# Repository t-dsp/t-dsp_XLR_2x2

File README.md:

# T-DSP XLR 2×2 — Balanced XLR I/O Board

**Part of the [T-DSP](https://t-dsp.com) open modular audio platform.**

A simple balanced-audio I/O board: **two XLR inputs and two XLR outputs** for pro line-level signals. It hosts a [T-DSP TAC5212 pro audio module](https://github.com/t-dsp/t-dsp_tac5212_pro_audio_module), which handles the entire analog signal path. Audio and control (I2S + I2C) are carried over a ribbon cable to a separate [T-DSP](https://t-dsp.com) controller module — this board has no microcontroller of its own.

| | |
|:---:|:---:|
|  |  |
|  |  |

**[View 3D Render Gallery](https://t-dsp.github.io/t-dsp_XLR_2x2/gallery.html)** -- interactive slideshow of all board views

## What It Is

This is a **balanced I/O carrier** for the T-DSP ecosystem. It exposes four panel-mount Neutrik XLR connectors and gives a [TAC5212 pro audio module](https://github.com/t-dsp/t-dsp_tac5212_pro_audio_module) a home:

- **2× XLR inputs** — balanced, pro line level, into the TAC5212 ADC
- **2× XLR outputs** — balanced, pro line level, from the TAC5212 DAC
- **TAC5212 module socket** — the codec daughter board mounts here and does all the analog work
- **Ribbon link** — I2S audio, I2C control, and power travel over a single 2×10 ribbon cable to the host controller

There is no microcontroller, DSP, or power supply on this board. It is purely the analog front panel: connectors, the codec module, and the cable to the brains.

## How It Fits Together

```
  XLR in  ─┐                                  ┌─ I2S (audio)
  XLR in  ─┼─►  TAC5212 module  ◄────ribbon───┼─ I2C (control)   ►  T-DSP controller
  XLR out ─┤      (this board)                └─ power              (Teensy-based)
  XLR out ─┘
```

The controller module runs the firmware and clocks; this board provides the balanced analog I/O and the codec that converts it.

## Features

### Audio I/O
- **2× balanced XLR input** — female XLR (Neutrik NC3FAH2), into the TAC5212 ADC
- **2× balanced XLR output** — male XLR (Neutrik NC3MAH), from the TAC5212 DAC
- Pro line-level signal path, handled entirely by the TAC5212 module

### Connectivity
- **TAC5212 module socket** — hosts the [T-DSP TAC5212 pro audio module](https://github.com/t-dsp/t-dsp_tac5212_pro_audio_module)
- **2×10 ribbon header** — carries I2S, I2C, and power to/from a T-DSP controller module

### Power
- Supplied from the host controller over the ribbon cable — no power input on this board

## Board Design

- **100 mm × 44 mm** PCB
- Built around the T-DSP audio module board-outline standard (50 × 34.5 mm module footprint)
- The TAC5212 module handles the entire analog signal path
- KiCad source files, full BOM, and CI-generated manufacturing outputs included
- Open source under CC BY-NC-SA 4.0

## Getting Started

### Hardware

1. Mount the **TAC5212 pro audio module** onto this board's module socket
2. Wire the four panel-mount **XLR connectors** (2 in, 2 out)
3. Connect the **2×10 ribbon cable** between this board and your T-DSP controller module
4. Power and clocks are provided by the controller over the ribbon — no separate supply needed

### Firmware

The TAC5212 codec is configured and clocked by the **host controller module**, not by this board. See [t-dsp_software](https://github.com/t-dsp/t-dsp_software) for the firmware that drives the codec over I2C and streams audio over I2S.

View the design files in your browser with KiCanvas: [Schematic](https://kicanvas.org/?github=https://github.com/t-dsp/t-dsp_XLR_2x2/blob/main/t-dsp_XLR_2x2.kicad_sch) | [PCB](https://kicanvas.org/?github=https://github.com/t-dsp/t-dsp_XLR_2x2/blob/main/t-dsp_XLR_2x2.kicad_pcb)

## Project Files

| Directory | Contents |
|-----------|----------|
| `/3d_models/` | 3D models for PCB components |
| `/lib_fp/` | Custom KiCad footprint libraries |
| `/lib_sch/` | Custom KiCad schematic symbol libraries |
| `/manufacturing/` | CI-generated manufacturing outputs (gerbers, BOM, pick & place, PDFs) |
| `/pages/` | [3D Render Gallery](https://t-dsp.github.io/t-dsp_XLR_2x2/gallery.html), [Interactive BOM](https://t-dsp.github.io/t-dsp_XLR_2x2/ibom.html) |

## Manufacturing

Manufacturing files are generated automatically by [KiBot](https://github.com/INTI-CMNB/KiBot) on every push to `main` and on tagged releases via GitHub Actions.

To order:
1. Download the latest `t-dsp_XLR_2x2-manufacturing-vX.X.zip` from [Releases](https://github.com/t-dsp/t-dsp_XLR_2x2/releases)
2. Upload gerbers and drill files to your PCB fab (JLCPCB, PCBWay, etc.)
3. Use the BOM and CPL files for JLCPCB SMT assembly

## About T-DSP

T-DSP is an open modular audio platform built around the Teensy microcontroller and the [Teensy Audio Library](https://www.pjrc.com/teensy/td_libs_Audio.html). This board is the balanced-I/O front end — a clean 2-in/2-out XLR interface that pairs a TAC5212 codec module with a T-DSP controller over a ribbon cable.

For a full audio development platform — a 4-layer backplane pairing a Teensy 4.1, an ESP32, and the TAC5212 codec module — see the [T-DSP Core](https://github.com/t-dsp/t-dsp_core).

Learn more at [t-dsp.com](https://t-dsp.com).

## Status

Active development. If you build one, please open an issue or reach out.

## Contact

For consulting, custom audio hardware design, or commercial licensing, reach out via [LinkedIn](https://linkedin.com/in/jayshoe).

## License

[Creative Commons Attribution-NonCommercial-ShareAlike 4.0 International (CC BY-NC-SA 4.0)](https://creativecommons.org/licenses/by-nc-sa/4.0/)

Free to share and adapt for non-commercial purposes with attribution and same license on derivatives.

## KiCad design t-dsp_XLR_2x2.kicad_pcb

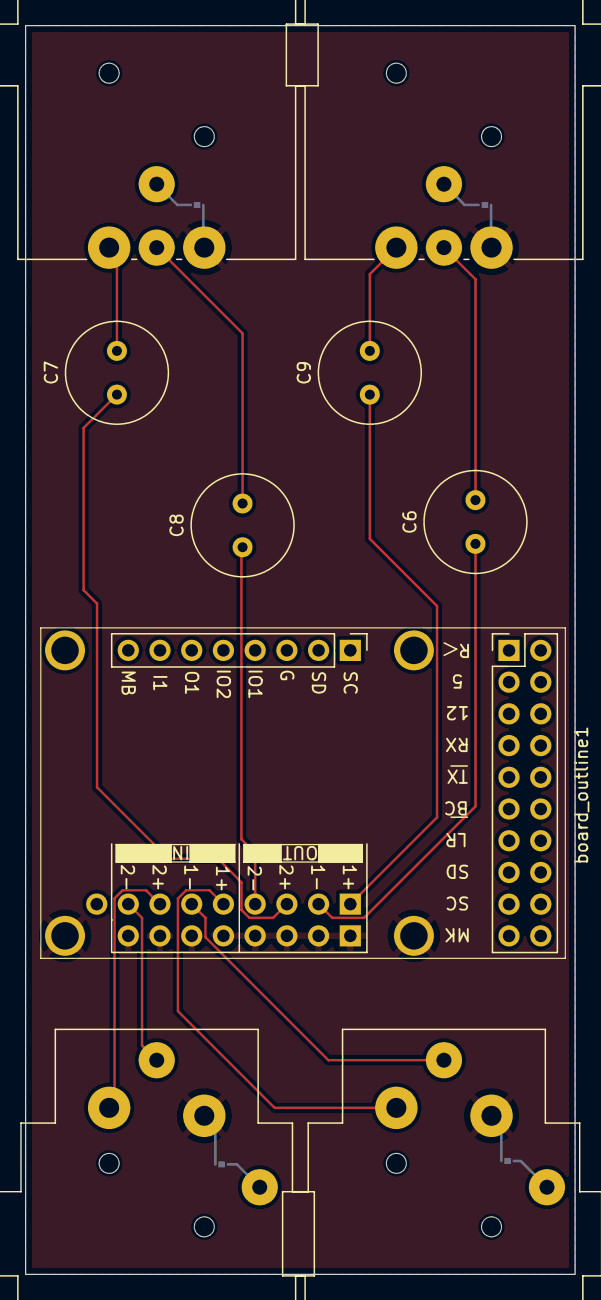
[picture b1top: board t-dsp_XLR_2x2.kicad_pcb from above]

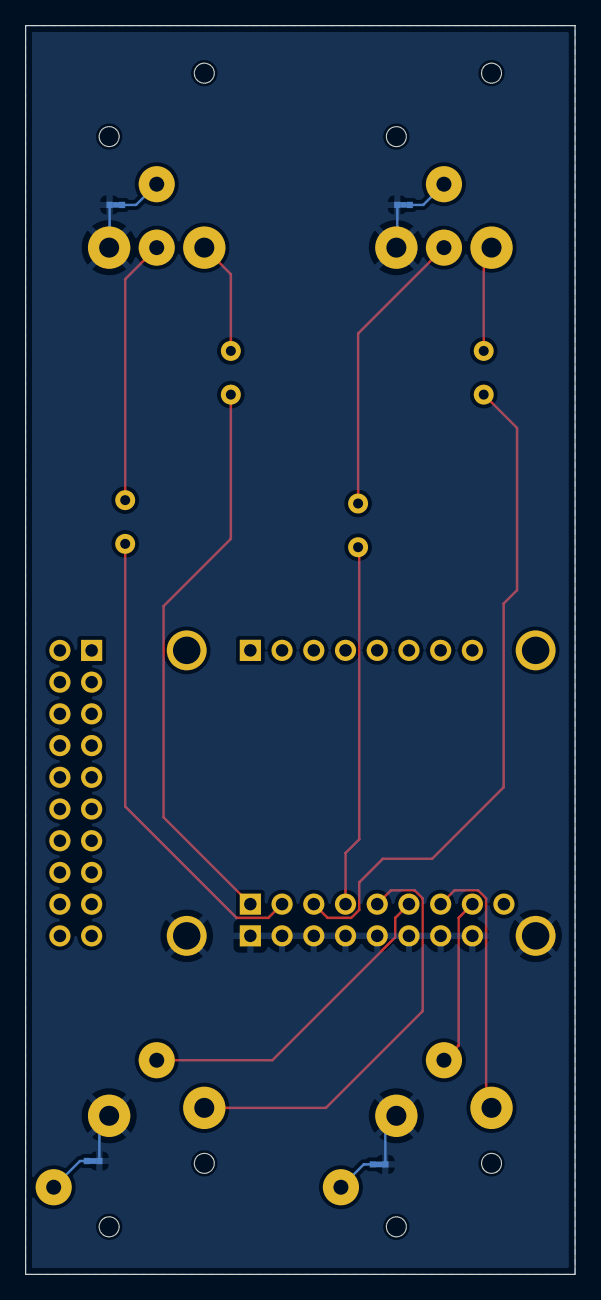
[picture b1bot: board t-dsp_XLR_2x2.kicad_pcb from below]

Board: 2 copper layers, 44.0 x 100.0 mm, 14 parts (4 on the bottom side), 17 nets.

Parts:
B1: Board; audio_project_board_outline_100x50_nm
C6, C7, C8, C9: 470 uF Electrolytic Audio-Grade; C_Radial_D8.0mm_H11.5mm_P3.50mm
G4, G5, G7, G8: jumper; jumper_slice
J30, J31: NC3FAH; Jack_XLR_Neutrik_NC3FAH2_Horizontal
XLRM1, XLRM2: XLRM_NC3MAH
board_outline1: TAC5212 Module; audio_module_board_outline_50x34.5_d1

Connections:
/AUDIO_IN1M: J30.3, board_outline1.31 (IN1M)
/AUDIO_IN1P: J30.2, board_outline1.29 (IN1P)
/AUDIO_IN2M: J31.3, board_outline1.35 (IN2M)
/AUDIO_IN2P: J31.2, board_outline1.33 (IN2P)
/AUDIO_OUT1M: C6.1, board_outline1.23 (OUT1M)
/AUDIO_OUT1P: C9.1, board_outline1.21 (OUTP)
/AUDIO_OUT2M: C8.1, board_outline1.27 (OUT2M)
/AUDIO_OUT2P: C7.1, board_outline1.25 (OUT2P)
Earth: G4.2, G5.2, G7.2, G8.2, J30.1, J31.1, XLRM1.1, XLRM2.1, board_outline1.22 (AGND), board_outline1.24 (AGND), board_outline1.26 (AGND), board_outline1.28 (AGND), board_outline1.30 (AGND), board_outline1.32 (AGND), board_outline1.34 (AGND), board_outline1.36 (AGND), board_outline1.49 (AGND), board_outline1.50 (AGND)
LEFT_LOM: C6.2, XLRM1.3
LEFT_LOP: C9.2, XLRM1.2
unnamed: G4.1, XLRM1.G
unnamed: G5.1, XLRM2.G
unnamed: G7.1, J30.G
unnamed: G8.1, J31.G
RIGHT_LOM: C8.2, XLRM2.3
RIGHT_LOP: C7.2, XLRM2.2

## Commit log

2026-03-10 update usb-a connector
2026-03-10 Update t-dsp_tac5212_audio_shield_adaptor.kicad_sch
    clean up BOM
2026-03-10 Update PCB layout
2026-03-14 Add new components, 3D models, and update PCB layout
    Add footprints and symbols for BLM15AG601SN1D, MSM261DGT003,
    PESD5V0F1BL_315, 35RAPC4BV4, and passive 0402 components.
    Add corresponding 3D models. Update schematic, PCB layout,
    and existing footprints.
2026-03-15 Fix ESD diode values and R13 value format for BOM correctness
2026-06-07 Rename project to t-dsp_XLR_2x2 and add XLR I/O footprints
    Rename the KiCad project files from t-dsp_tac5212_audio_shield_adaptor to t-dsp_XLR_2x2. Add Neutrik NC3FAH/NC3FAH2 XLR footprints, 3D models, board outlines, and supporting library updates for the 2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
2026-06-07 Rewrite README for XLR 2x2 balanced I/O board
    Replace inherited Teensy-shield docs with accurate description: 2x XLR in + 2x XLR out for pro line level, hosting a TAC5212 pro audio module linked to a T-DSP controller over a 2x10 ribbon (I2S/I2C/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
2026-06-07 README: point to T-DSP Core instead of discontinued Desktop Pro
